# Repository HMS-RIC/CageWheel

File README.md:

# CageWheel

A RaspberryPi-based system for monitoring running wheels in up to 24 mouse cages.

## Instructions for setting up new Pi for Mouse Wheel Controller

### 1. Flash new SD card with Raspbian
- Get latest Raspbian from https://www.raspberrypi.org/downloads/raspbian/
	- Probably don't need full version with "recommended software"
- Use BalenaEtcher to flash it on to SD card

### 2. Boot up Pi
- Raspbian will ask for some setup information:
	- set language & time zone
	- set password: "mouse run fast"
- Create a new folder ~/bin
- Copy `CageWheelMonitor.py` to ~/bin
- Make `CageWheelMonitor.py` executable
	- open a terminal and type: `chmod +x ~/bin/CageWheelMonitor.py`
- You may need to log our and log back in before you can run it

You should be good to go!

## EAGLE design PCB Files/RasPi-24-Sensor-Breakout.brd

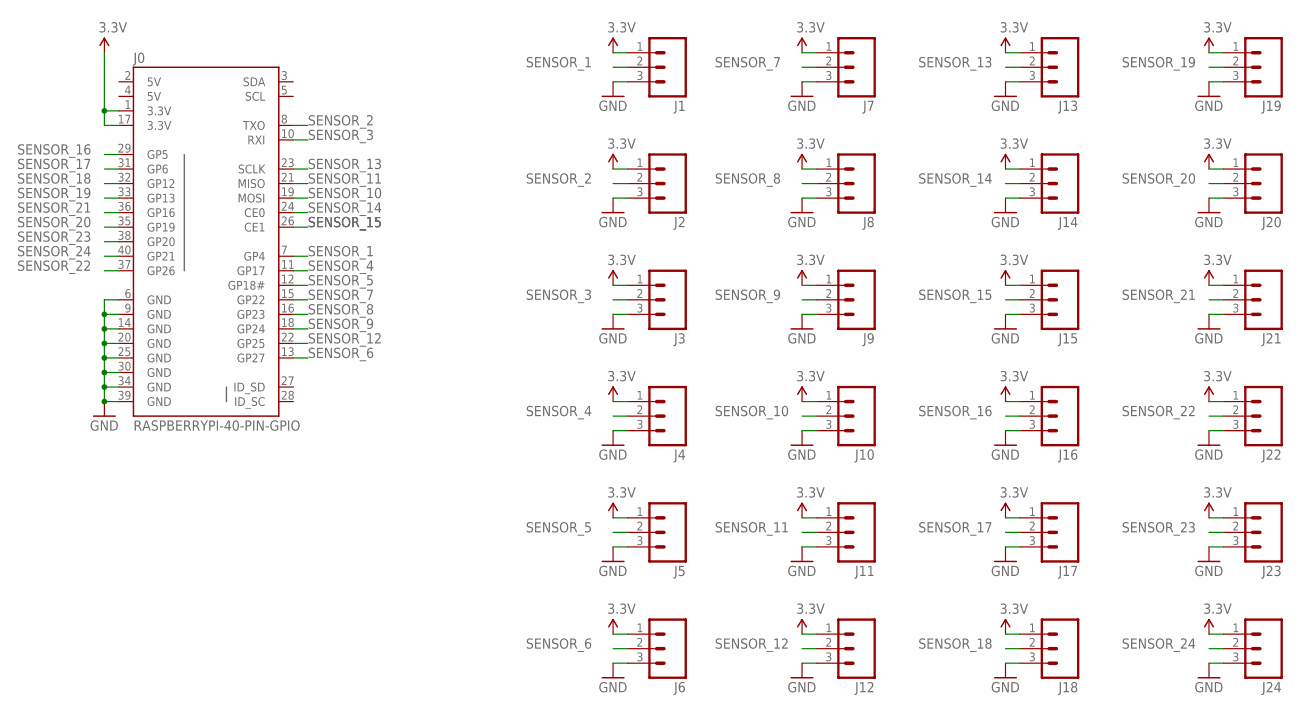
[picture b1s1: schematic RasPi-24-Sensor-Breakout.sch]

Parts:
J0: RASPBERRYPI-40-PIN-GPIO; 2X20-SHROUDED
J1, J2, J3, J4, J5, J6, J7, J8, J9, J10, J11, J12, J13, J14, J15, J16, J17, J18, J19, J20, J21, J22, J23, J24: M03POLAR; MOLEX-1X3

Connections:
3.3V: J0.1 (3.3V), J0.17 (3.3V), J1.1, J2.1, J3.1, J4.1, J5.1, J6.1, J7.1, J8.1, J9.1, J10.1, J11.1, J12.1, J13.1, J14.1, J15.1, J16.1, J17.1, J18.1, J19.1, J20.1, J21.1, J22.1, J23.1, J24.1
5V: J0.2 (5V), J0.4 (5V)
GND: J0.6 (GND), J0.9 (GND), J0.14 (GND), J0.20 (GND), J0.25 (GND), J0.30 (GND), J0.34 (GND), J0.39 (GND), J1.3, J2.3, J3.3, J4.3, J5.3, J6.3, J7.3, J8.3, J9.3, J10.3, J11.3, J12.3, J13.3, J14.3, J15.3, J16.3, J17.3, J18.3, J19.3, J20.3, J21.3, J22.3, J23.3, J24.3
SENSOR_1: J0.7 (GP4), J1.2
SENSOR_2: J0.8 (TXO), J2.2
SENSOR_3: J0.10 (RXI), J3.2
SENSOR_4: J0.11 (GP17), J4.2
SENSOR_5: J0.12 (GP18#), J5.2
SENSOR_6: J0.13 (GP27), J6.2
SENSOR_7: J0.15 (GP22), J7.2
SENSOR_8: J0.16 (GP23), J8.2
SENSOR_9: J0.18 (GP24), J9.2
SENSOR_10: J0.19 (MOSI), J10.2
SENSOR_11: J0.21 (MISO), J11.2
SENSOR_12: J0.22 (GP25), J12.2
SENSOR_13: J0.23 (SCLK), J13.2
SENSOR_14: J0.24 (CE0), J14.2
SENSOR_15: J0.26 (CE1), J15.2
SENSOR_16: J0.29 (GP5), J16.2
SENSOR_17: J0.31 (GP6), J17.2
SENSOR_18: J0.32 (GP12), J18.2
SENSOR_19: J0.33 (GP13), J19.2
SENSOR_20: J0.35 (GP19), J20.2
SENSOR_21: J0.36 (GP16), J21.2
SENSOR_22: J0.37 (GP26), J22.2
SENSOR_23: J0.38 (GP20), J23.2
SENSOR_24: J0.40 (GP21), J24.2

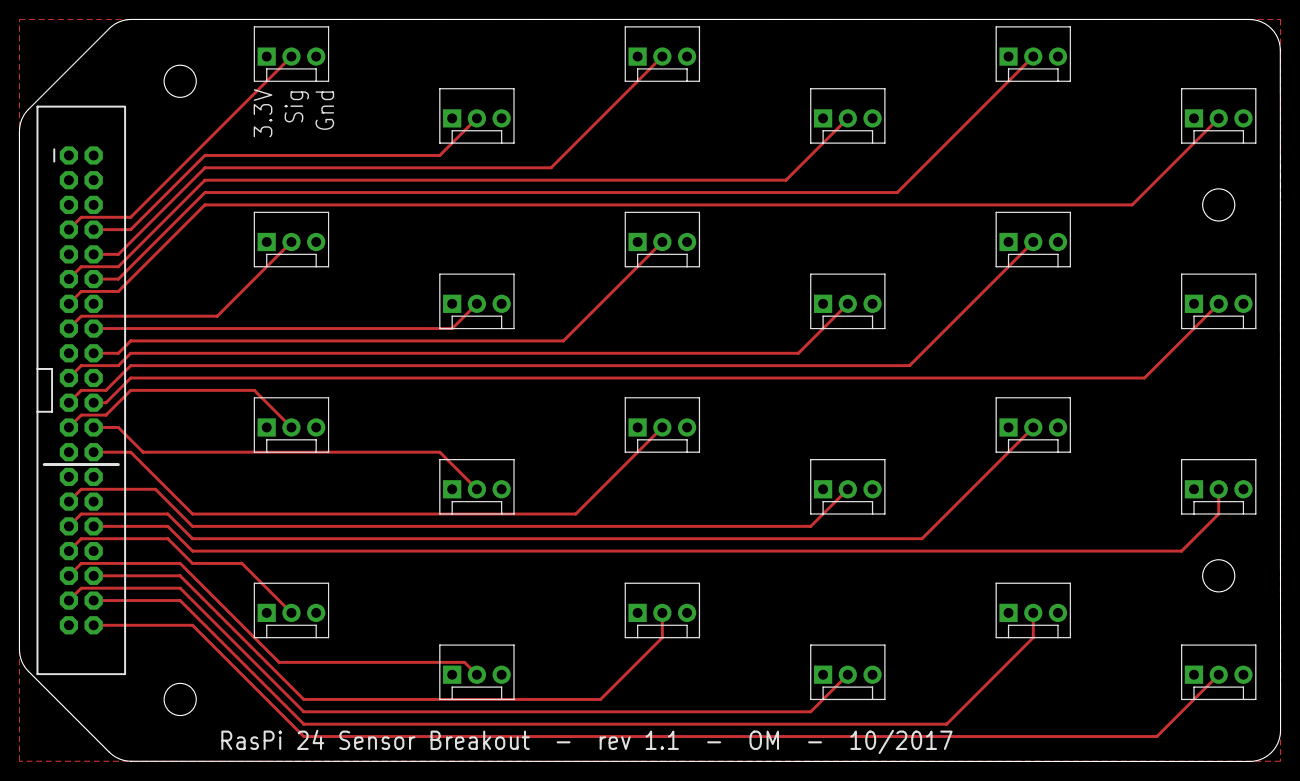
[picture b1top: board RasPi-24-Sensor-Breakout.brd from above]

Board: 2 copper layers, 129.5 x 76.2 mm, 29 parts (0 on the bottom side), 27 nets.

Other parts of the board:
U$1, U$2, U$3, U$4: STAND-OFF

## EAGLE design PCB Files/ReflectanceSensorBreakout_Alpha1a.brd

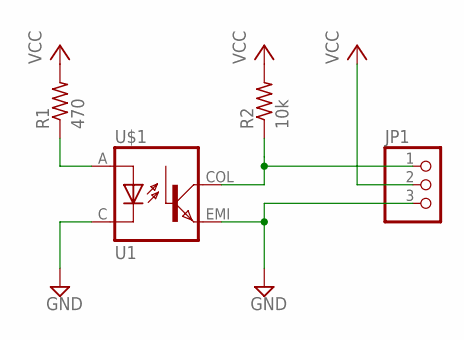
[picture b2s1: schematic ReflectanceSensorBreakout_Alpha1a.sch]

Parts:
JP1: PINHD-1X3; 1X03
R1: 470; 0204/7
R2: 10k; 0204/7
U$1: U1; ADAFRUIT_REFLECTANCE_SENSOR

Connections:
GND: JP1.3, U$1.C, U$1.EMI
unnamed: R1.1, U$1.A
unnamed: JP1.1, R2.1, U$1.COL
VCC: JP1.2, R1.2, R2.2

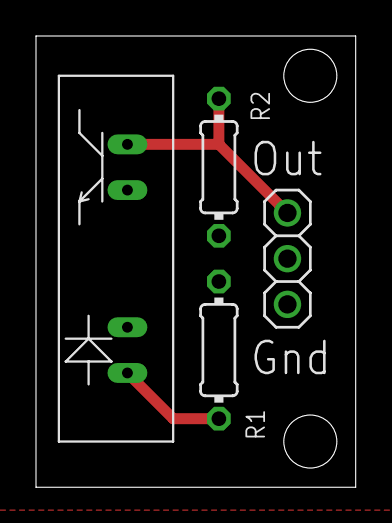
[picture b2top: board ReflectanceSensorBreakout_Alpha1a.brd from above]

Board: 2 copper layers, 17.8 x 25.1 mm, 4 parts (0 on the bottom side), 4 nets.

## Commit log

2017-08-30 fixed calculations of revs per sec
2017-08-30 cleaned up callback code
2017-08-31 fixed log file formatting
2017-09-15 Create LICENSE
2017-09-15 Detect RasPi baord type and uses all available GPIO pins; Log files are broken into 24-h chunks.
2017-09-26 fixed crash in pin listing code
2017-09-27 fixed crash in multi-log file code
2017-10-04 fixed gpio bug
2017-10-04 Output to screen is more imformation-dense (better for more mice)
2017-10-13 Log files: Added "#" before header information.
2017-10-13 removed leading space from first line of script
2018-03-02 added pause to let gpio daemon start up.

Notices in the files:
parts and their libraries:
SparkFun-Connectors: Licensing: Creative Commons ShareAlike 4.0 International - https://creativecommons.org/licenses/by-sa/4.0
